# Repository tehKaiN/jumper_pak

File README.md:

# Jumper Pak

<div style="display: flex; flex-direction: row; justify-content: center;">

</div>

This is an open-source Nintendo 64 Jumper Pak replacement.
Dimensions are captured from the original with caliper, with slight modifications.
Design is based on high resolution scans of the original and scraps of information found across the Internet.

I was commissioned to do this, and I don't have the actual hardware, but the project was tested by other people and proven to work.
The PCB contains the footprints for both resistor packs as well as single 0603 resistors.
**Don't solder both of them! Choose one type!**

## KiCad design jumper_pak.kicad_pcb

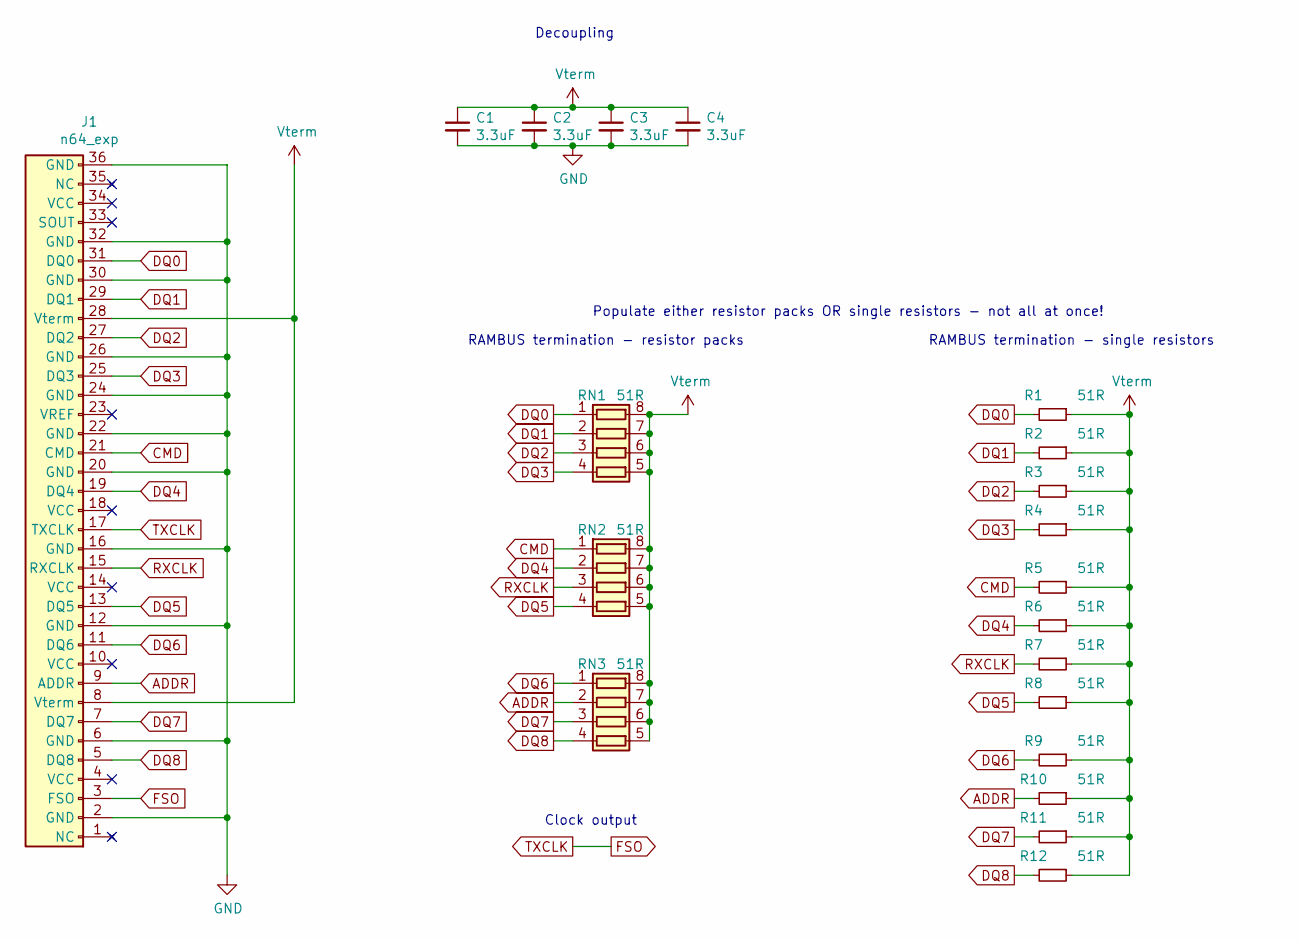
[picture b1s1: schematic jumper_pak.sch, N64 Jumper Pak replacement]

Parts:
C1, C2, C3, C4: 3.3uF; C_0603_1608Metric
J1: n64_exp; ram-pak-edge-conn
R1, R2, R3, R4, R5, R6, R7, R8, R9, R10, R11, R12: 51R; R_0603_1608Metric
RN1, RN2, RN3: 51R; R_Array_Convex_4x0603

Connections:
ADDR: J1.9 (ADDR), R10.2, RN3.2 (R2.1)
CMD: J1.21 (CMD), R5.2, RN2.1 (R1.1)
DQ0: J1.31 (DQ0), R1.2, RN1.1 (R1.1)
DQ1: J1.29 (DQ1), R2.2, RN1.2 (R2.1)
DQ2: J1.27 (DQ2), R3.2, RN1.3 (R3.1)
DQ3: J1.25 (DQ3), R4.2, RN1.4 (R4.1)
DQ4: J1.19 (DQ4), R6.2, RN2.2 (R2.1)
DQ5: J1.13 (DQ5), R8.2, RN2.4 (R4.1)
DQ6: J1.11 (DQ6), R9.2, RN3.1 (R1.1)
DQ7: J1.7 (DQ7), R11.2, RN3.3 (R3.1)
DQ8: J1.5 (DQ8), R12.2, RN3.4 (R4.1)
FSO: J1.3 (FSO), J1.17 (TXCLK)
GND: C1.2, C2.2, C3.2, C4.2, J1.2 (GND), J1.6 (GND), J1.12 (GND), J1.16 (GND), J1.20 (GND), J1.22 (GND), J1.24 (GND), J1.26 (GND), J1.30 (GND), J1.32 (GND), J1.36 (GND)
RXCLK: J1.15 (RXCLK), R7.2, RN2.3 (R3.1)
VCC: C1.1, C2.1, C3.1, C4.1, J1.8 (Vterm), J1.28 (Vterm), R1.1, R2.1, R3.1, R4.1, R5.1, R6.1, R7.1, R8.1, R9.1, R10.1, R11.1, R12.1, RN1.5 (R4.2), RN1.6 (R3.2), RN1.7 (R2.2), RN1.8 (R1.2), RN2.5 (R4.2), RN2.6 (R3.2), RN2.7 (R2.2), RN2.8 (R1.2), RN3.5 (R4.2), RN3.6 (R3.2), RN3.7 (R2.2), RN3.8 (R1.2)

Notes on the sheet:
Decoupling
RAMBUS termination - resistor packs
Clock output
RAMBUS termination - single resistors
Populate either resistor packs OR single resistors - not all at once!

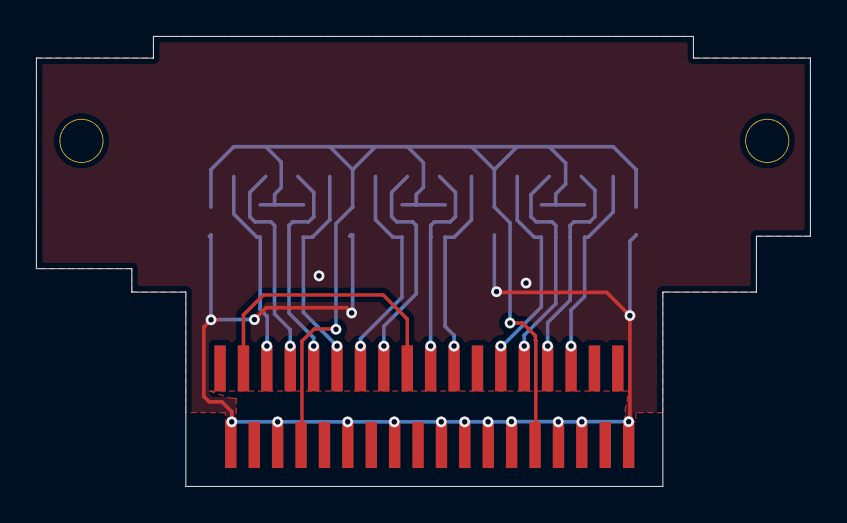
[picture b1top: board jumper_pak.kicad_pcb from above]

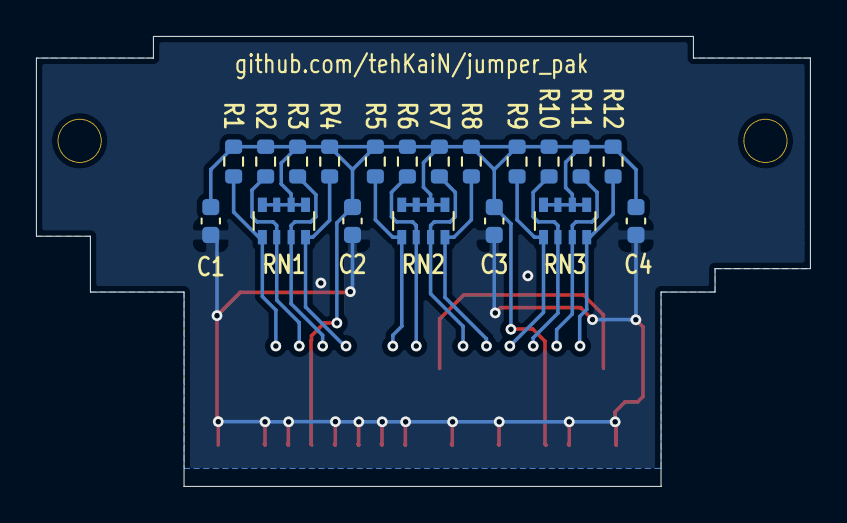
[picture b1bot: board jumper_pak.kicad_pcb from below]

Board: 2 copper layers, 43.0 x 25.0 mm, 20 parts (19 on the bottom side), 15 nets.

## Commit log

2022-12-03 added README.md
2022-12-03 added license
